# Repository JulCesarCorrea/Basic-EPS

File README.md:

# Missão Samaúma – Detecção Orbital de Pistas Clandestinas na Amazônia

## Introdução
A Amazônia desempenha um papel estratégico de extrema relevância global e nacional, abrigando a maior biodiversidade do planeta e recursos naturais de alto valor. Contudo, essa importância é 
ameaçada pela proliferação de pistas de pouso clandestinas, que funcionam como vetores para atividades ilícitas como garimpo ilegal, narcotráfico e desmatamento, comprometendo o equilíbrio ambiental,
social e a soberania nacional.
Estudos apontam que há mais pistas não homologadas do que oficiais na Amazônia Legal, formando uma infraestrutura paralela que impulsiona essas atividades ilegais.

Apesar dos esforços de fiscalização, o monitoramento por satélites convencionais enfrenta limitações significativas:
- Baixa frequência de revisita orbital, dificultando a detecção em tempo hábil.
- Alta latência entre a aquisição e o processamento das imagens.
- Custos elevados de obtenção e manutenção de imagens atualizadas.
- Diante desses desafios, a Missão Samaúma propõe o desenvolvimento de um CubeSat 1U de baixo custo com inteligência artificial embarcada capaz de realizar imageamento orbital autônomo e detecção
em tempo real de pistas clandestinas.

**O satélite processa as imagens diretamente em órbita e envia alertas com dados de localização e área estimada, reduzindo custos, latência e dependência de infraestrutura terrestre.
O projeto reforça a pesquisa em monitoramento ambiental com tecnologias acessíveis e contribui para o avanço da IA embarcada em CubeSats, com impacto direto na soberania e proteção da Amazônia.**

### Equipe e Responsabilidades

A Missão Samaúma é conduzida por dois estudantes de Engenharia de Computação do Instituto Nacional de Telecomunicações (INATEL), sob orientação técnica do Prof. Evandro César Vilas Boas.

### Membros, Funções e	Responsabilidades
- Mateus Ananias Duarte Lima	Software e IA embarcada	Desenvolvimento do algoritmo de detecção de pistas; implementação do sistema operacional de tempo real (RTOS); integração dos subsistemas via software.
- Daniele Letícia Pereira Sousa	Hardware e sistemas embarcados	Projeto e implementação dos subsistemas físicos (EPS, STR, Payload, COMMS, TCS, ADCS); integração e validação de hardware.

- Apesar da divisão de responsabilidades, o trabalho é conduzido de forma colaborativa e integrada, permitindo que ambos mantenham visão global do projeto e contribuam em múltiplas frentes técnicas.

## Descrição Operacional

A Missão Samaúma é estruturada em três etapas principais:
- Mapeamento e pesquisa inicial
- Identificação de áreas críticas com maior ocorrência de desmatamento, indicativas de potenciais pistas irregulares.
- Imageamento orbital via CubeSat
- Coleta de imagens nas regiões mapeadas, utilizando sensores ópticos embarcados.

### Processamento e análise por IA
O algoritmo embarcado processa as imagens diretamente no computador de bordo (OBC), distinguindo áreas de desmatamento comum de pistas clandestinas, e enviando alertas automáticos com coordenadas 
e área estimada.

## Tecnologias e Conceitos-Chave
- CubeSat 1U – Plataforma modular de baixo custo para missões orbitais.
- IA Embarcada (On-board Processing) – Reduz latência e dependência de links terrestres.
- RTOS (Real-Time Operating System) – Assegura eficiência e previsibilidade na execução das tarefas do satélite.
- Detecção Autônoma de Pistas – Uso de visão computacional e aprendizado de máquina para classificação de imagens orbitais.

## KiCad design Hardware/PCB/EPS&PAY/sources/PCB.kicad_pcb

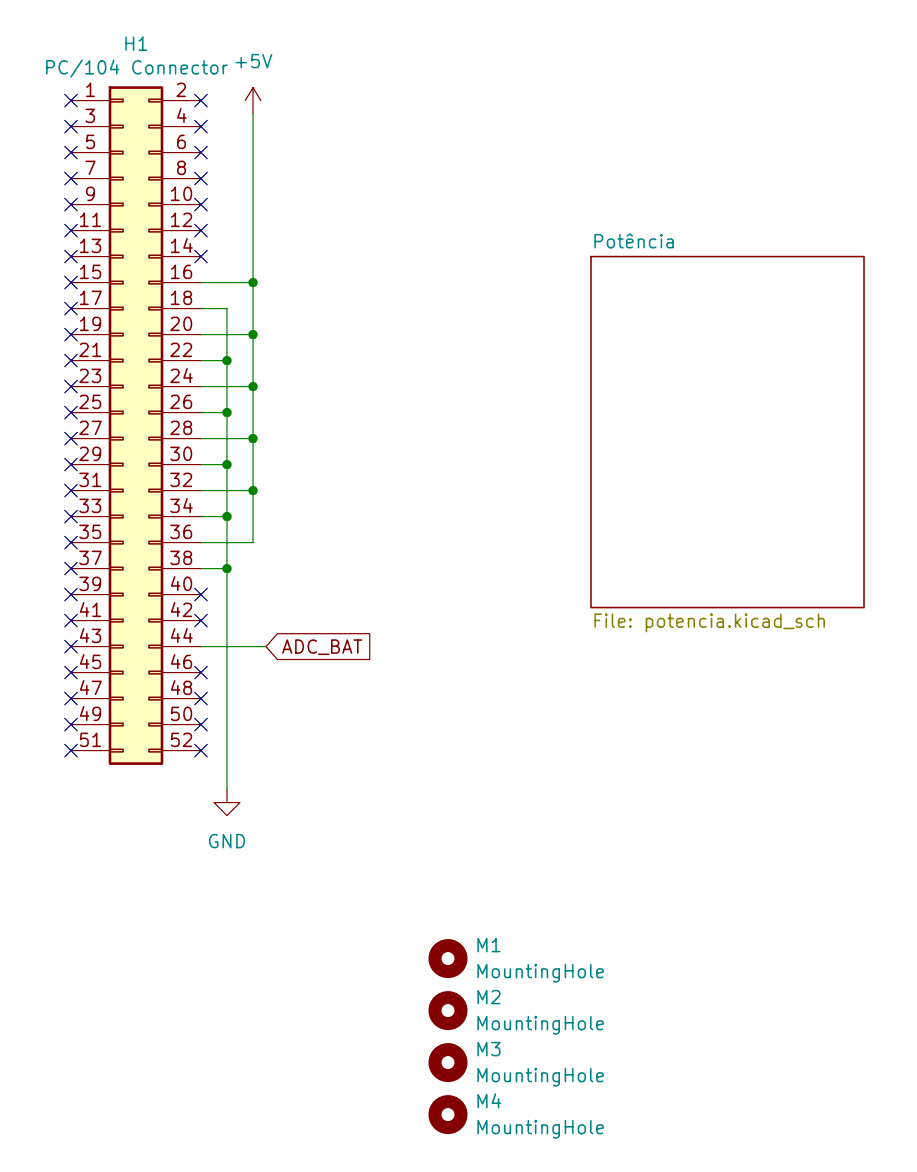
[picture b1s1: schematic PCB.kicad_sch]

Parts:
H1: PC/104 Connector; PinSocket_2x26_P2.54mm_Vertical
M1, M2, M3, M4: MountingHole; MountingHole_3.2mm_M3_Pad

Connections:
+5V: H1.16, H1.20, H1.24, H1.28, H1.32, H1.36; also elsewhere on the board
ADC_BAT: H1.44; also elsewhere on the board
GND: H1.18, H1.22, H1.26, H1.30, H1.34, H1.38; also elsewhere on the board

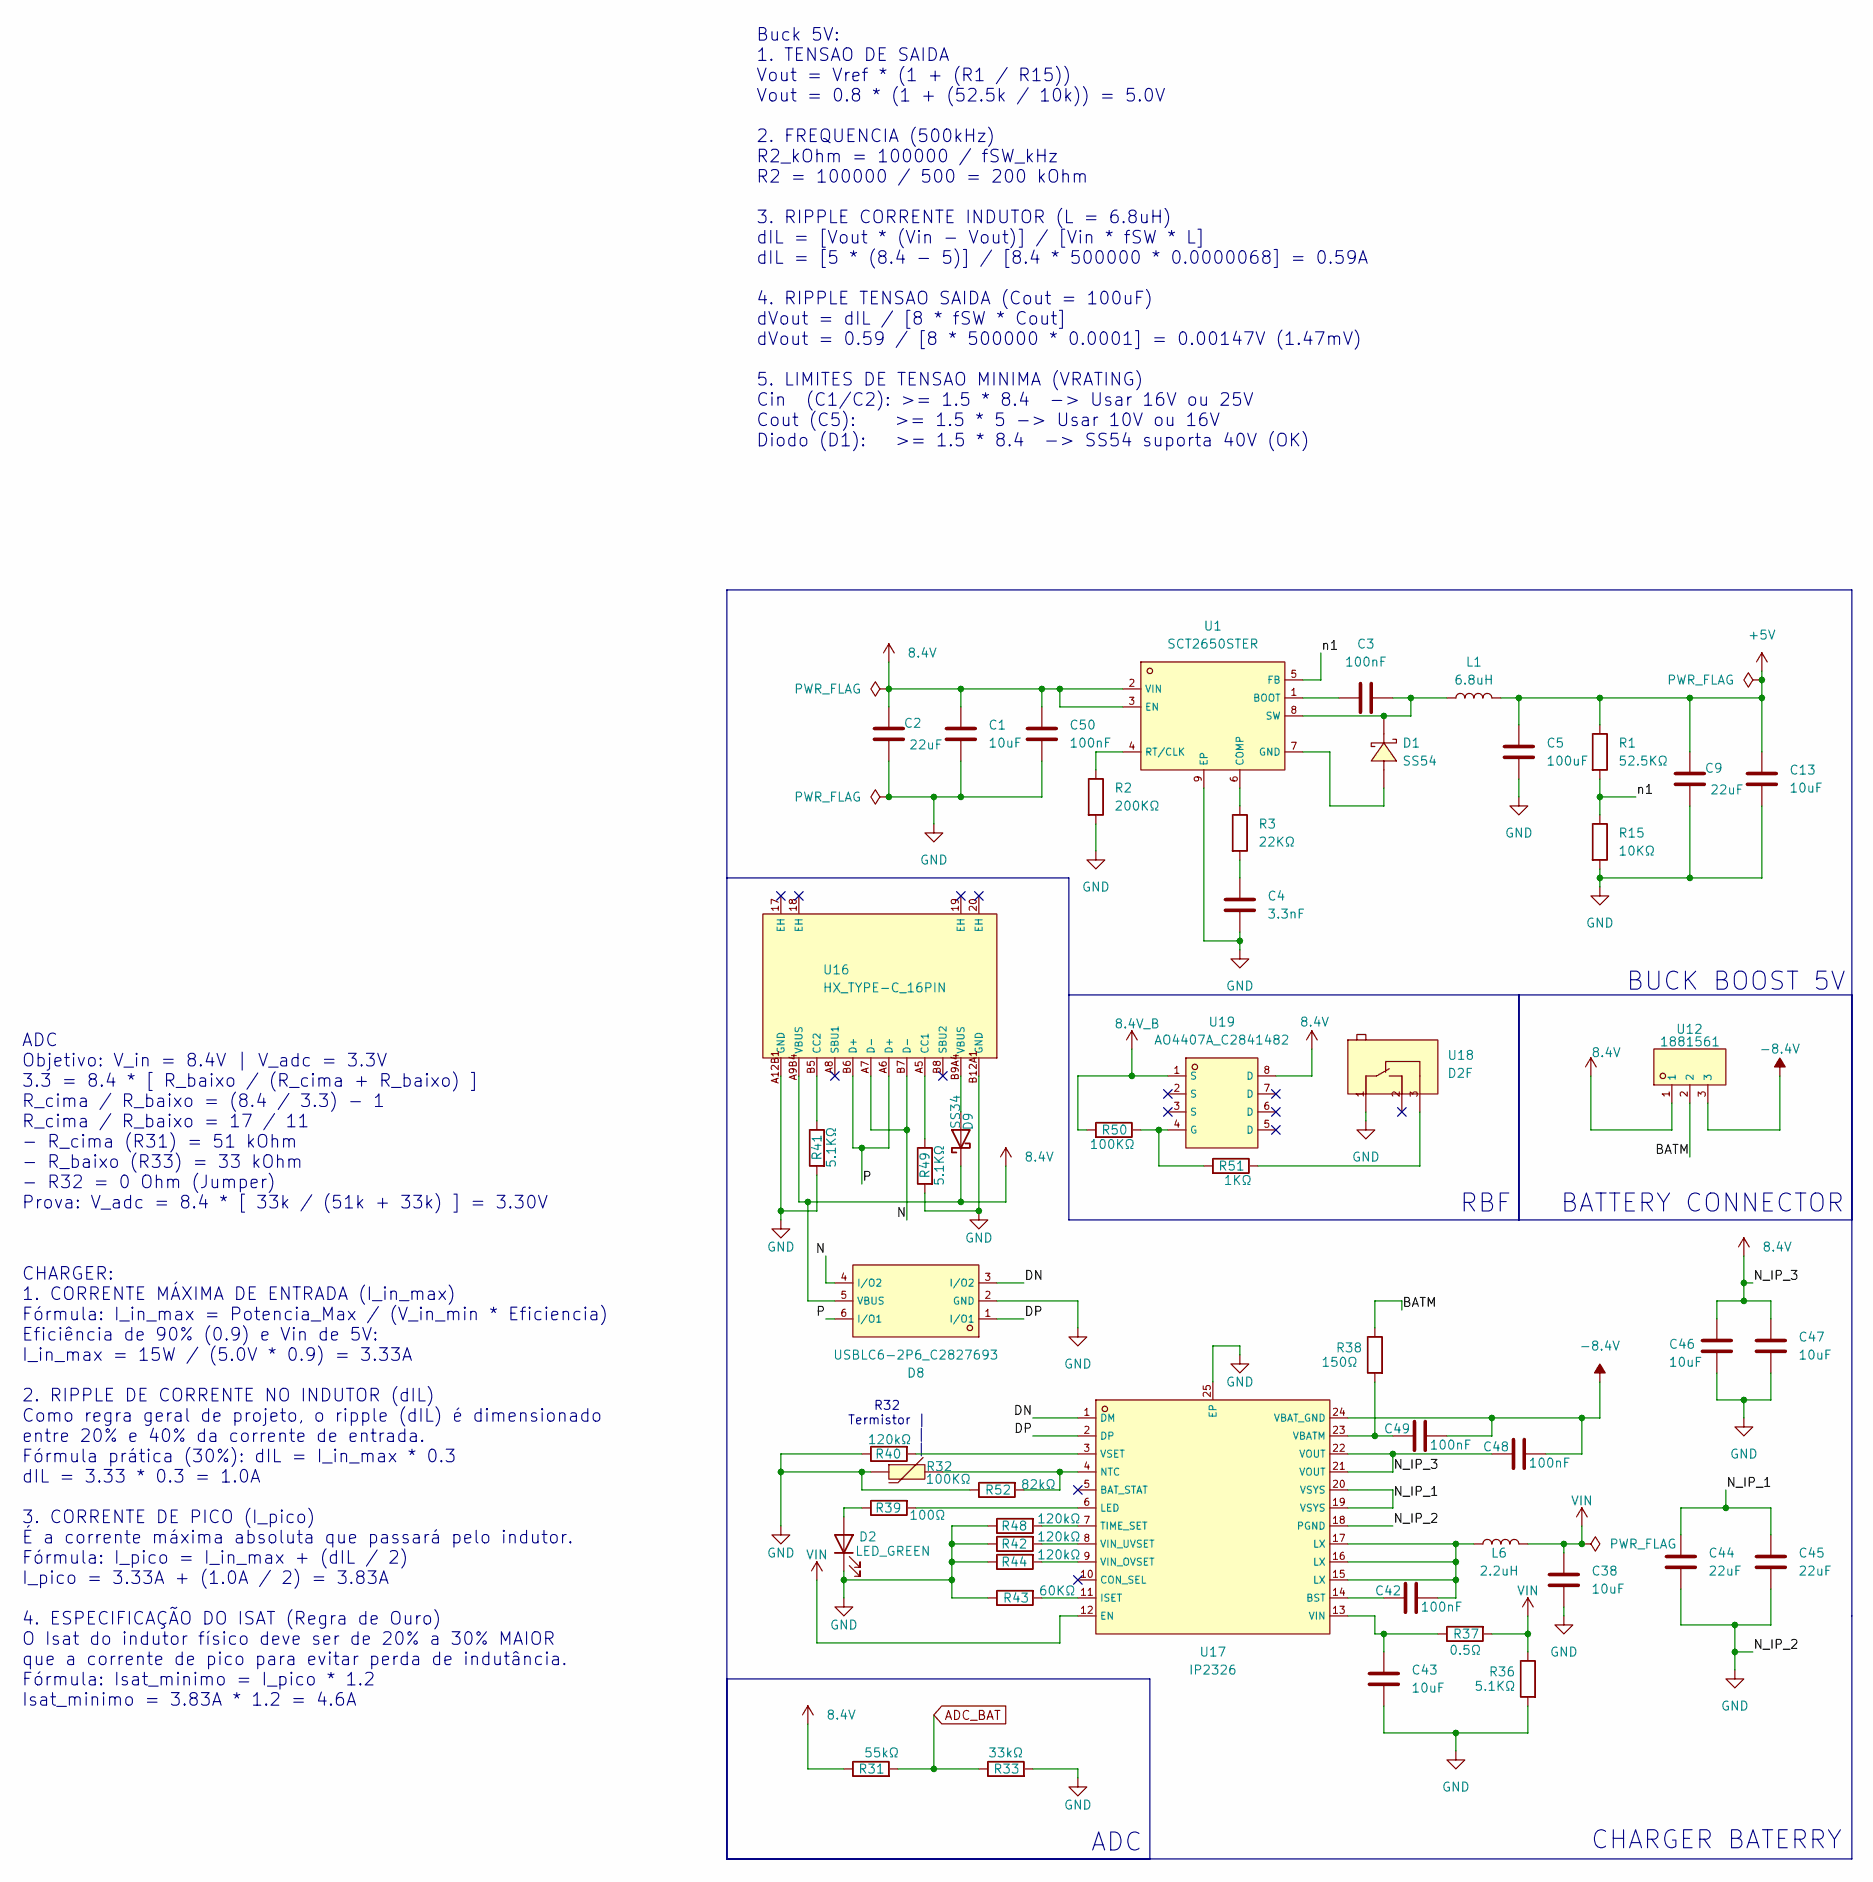
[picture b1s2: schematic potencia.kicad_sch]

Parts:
C1, C13, C38, C43, C46, C47: 10uF; C0805; LCSC C440198
C2, C9, C44, C45: 22uF; C1206; LCSC C3038553
C3, C42, C48, C49, C50: 100nF; C0603; LCSC C14663
C4: 3.3nF; C0603; LCSC C1613
C5: 100uF; C1206; LCSC C3038553
D1: SS54; SMB_L4.3-W3.6-LS5.4-RD; LCSC C5200096
D2: LED_GREEN; LED0603-FD; LCSC C19273151
D8: USBLC6-2P6_C2827693; SOT-666-6_L1.6-W1.2-P0.50-LS1.6-BL; LCSC C2827693
D9: SS34; D_SMA
L1: 6.8uH; IND-SMD_L5.4-W5.2; LCSC C718382
L6: 2.2uH; L1008; LCSC C42455362
R1: 52.5KΩ; R0402; LCSC C2998086
R2: 200KΩ; R0603; LCSC C2907009
R3: 22KΩ; R0603; LCSC C2907015
R15: 10KΩ; R0603; LCSC C98220
R31: 55kΩ; R_0603_1608Metric_Pad0.98x0.95mm_HandSolder; LCSC C2933461
R32: 100KΩ; R0603; LCSC C71280
R33: 33kΩ; R_1206_3216Metric_Pad1.30x1.75mm_HandSolder; LCSC C2933415
R36, R41, R49: 5.1KΩ; R0603; LCSC C2907044
R37: 0.5Ω; RES-SMD_L6.4-W3.2-R2512; LCSC C2904268
R38: 150Ω; R0603; LCSC C2933324
R39: 100Ω; R0603; LCSC C2906981
R40, R42, R44, R48: 120kΩ; R0603; LCSC C25808
R43: 60KΩ; R0603; LCSC C2907044
R50: 100KΩ; R0603; LCSC C14675
R51: 1KΩ; R0603; LCSC C22548
R52: 82kΩ; R0402; LCSC C2909388
U1: SCT2650STER; ESOP-8_L4.9-W3.9-P1.27-LS6.0-BL-EP-2; LCSC C2840771
U12: 1881561; CONN-TH_3P-P2.50_C3585554; LCSC C3585554
U16: HX_TYPE-C_16PIN; TYPE-C-SMD_HX-TYPE-C-16PIN; LCSC C5178539
U17: IP2326; VQFN-24_L4.0-W4.0-P0.50-BL-EP2.5; LCSC C2832094
U18: D2F; SW-TH_D2F-L; LCSC C397279
U19: AO4407A_C2841482; SOP-8_L5.0-W4.0-P1.27-LS6.0-BL; LCSC C2841482

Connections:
8.4V: C1.1, C2.1, C46.1, C47.1, C48.2, C50.2, D8.5 (VBUS), D9.1 (K), R31.1, U1.2 (VIN), U1.3 (EN), U12.1, U16.A9B4 (VBUS), U17.21 (VOUT), U17.22 (VOUT), U19.8 (D)
8.4V_B: R50.2, U19.1 (S)
+5V: C5.1, C9.1, C13.1, L1.2, R1.1; also elsewhere on the board
-8.4V: C48.1, C49.1, U12.3, U17.24 (VBAT_GND)
/Potência/BATM: R38.1, U12.2
/Potência/DN: D8.3 (I/O2), U17.1 (DM)
/Potência/DP: D8.1 (I/O1), U17.2 (DP)
/Potência/N: D8.4 (I/O2), U16.A7 (D-), U16.B7 (D-)
/Potência/N_IP_1: C44.1, C45.1, U17.19 (VSYS), U17.20 (VSYS)
/Potência/P: D8.6 (I/O1), U16.A6 (D+), U16.B6 (D+)
/Potência/n1: R1.2, R15.1, U1.5 (FB)
ADC_BAT: R31.2, R33.1; also elsewhere on the board
GND: C1.2, C2.2, C4.2, C5.2, C9.2, C13.2, C38.2, C43.2, C44.2, C45.2, C46.2, C47.2, C50.1, D2.1 (K), D8.2 (GND), R2.2, R15.2, R32.1, R33.2, R36.2, R40.1, R41.2, R42.1, R43.1, R44.1, R48.1, R49.2, R52.1, U1.9 (EP), U16.A12B1 (GND), U16.B12A1 (GND), U17.18 (PGND), U17.25 (EP), U18.1 (COM); also elsewhere on the board
unnamed: C4.1, R3.2
unnamed: C42.1, L6.1, U17.15 (LX), U17.16 (LX), U17.17 (LX)
unnamed: D2.2 (A), R39.1
unnamed: D9.2 (A), U16.B9A4 (VBUS)
unnamed: C3.1, U1.1 (BOOT)
unnamed: R3.1, U1.6 (COMP)
unnamed: D1.2, U1.7 (GND)
unnamed: R2.1, U1.4 (RT/CLK)
unnamed: C3.2, D1.1, L1.1, U1.8 (SW)
unnamed: R49.1, U16.A5 (CC1)
unnamed: R41.1, U16.B5 (CC2)
unnamed: C42.2, U17.14 (BST)
unnamed: R43.2, U17.11 (ISET)
unnamed: R39.2, U17.6 (LED)
unnamed: R32.2, R52.2, U17.4 (NTC)
unnamed: R48.2, U17.7 (TIME_SET)
unnamed: C49.2, R38.2, U17.23 (VBATM)
unnamed: C43.1, R37.1, U17.13 (VIN)
unnamed: R44.2, U17.9 (VIN_OVSET)
unnamed: R42.2, U17.8 (VIN_UVSET)
unnamed: R40.2, U17.3 (VSET)
unnamed: R51.1, U18.3 (NC)
unnamed: R50.1, R51.2, U19.4 (G)
VIN: C38.1, L6.2, R36.1, R37.2, U17.12 (EN)

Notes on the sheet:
CHARGER BATERRY
Buck 5V: 1. TENSAO DE SAIDA Vout = Vref * (1 + (R1 / R15)) Vout = 0.8 * (1 + (52.5k / 10k)) = 5.0V 2. FREQUENCIA (500kHz) R2_kOhm = 100000 / fSW_kHz R2 = 100000 / 500 = 200 kOhm 3. RIPPLE CORRENTE INDUTOR (L = 6.8uH) dIL = [Vout * (Vin - Vout)] / [Vin * fSW * L] dIL = [5 * (8.4 - 5)] / [8.4 * 50000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
BUCK BOOST 5V
ADC Objetivo: V_in = 8.4V | V_adc = 3.3V 3.3 = 8.4 * [ R_baixo / (R_cima + R_baixo) ] R_cima / R_baixo = (8.4 / 3.3) - 1 R_cima / R_baixo = 17 / 11 - R_cima (R31) = 51 kOhm - R_baixo (R33) = 33 kOhm - R32 = 0 Ohm (Jumper) Prova: V_adc = 8.4 * [ 33k / (51k + 33k) ] = 3.30V
CHARGER: 1. CORRENTE MÁXIMA DE ENTRADA (I_in_max) Fórmula: I_in_max = Potencia_Max / (V_in_min * Eficiencia) Eficiência de 90% (0.9) e Vin de 5V: I_in_max = 15W / (5.0V * 0.9) = 3.33A 2. RIPPLE DE CORRENTE NO INDUTOR (dIL) Como regra geral de projeto, o ripple (dIL) é dimensionado entre 20% e 40% d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
R32 Termistor | | |
BATTERY CONNECTOR
ADC
RBF

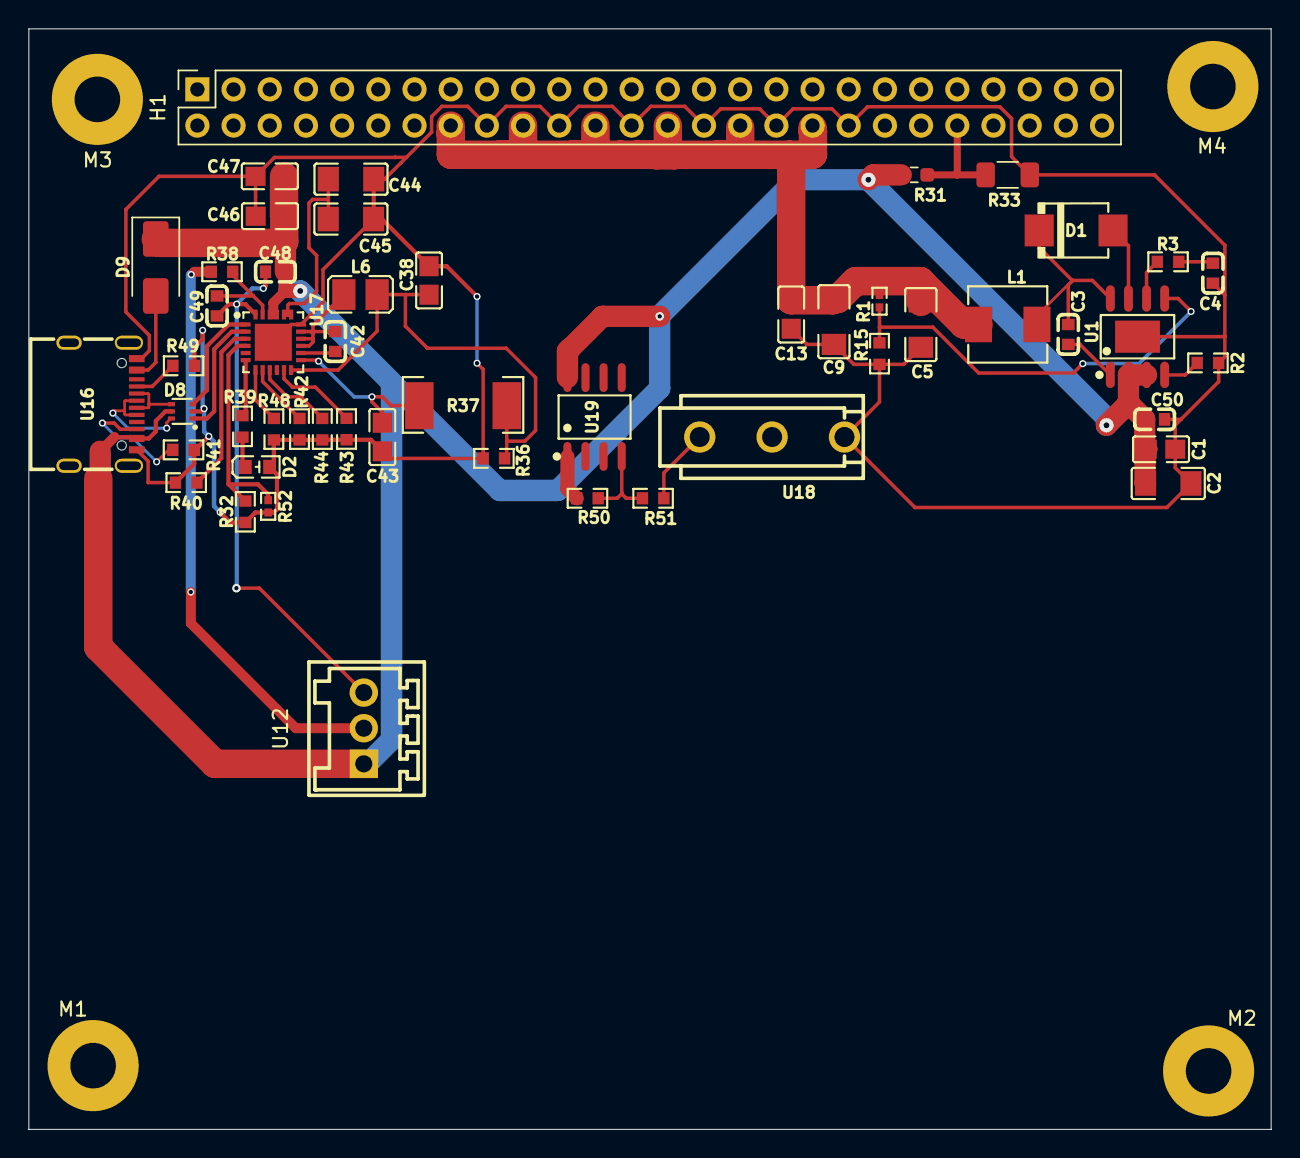
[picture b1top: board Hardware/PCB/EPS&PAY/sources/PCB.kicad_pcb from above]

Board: 2 copper layers, 87.2 x 77.2 mm, 55 parts (0 on the bottom side), 37 nets.

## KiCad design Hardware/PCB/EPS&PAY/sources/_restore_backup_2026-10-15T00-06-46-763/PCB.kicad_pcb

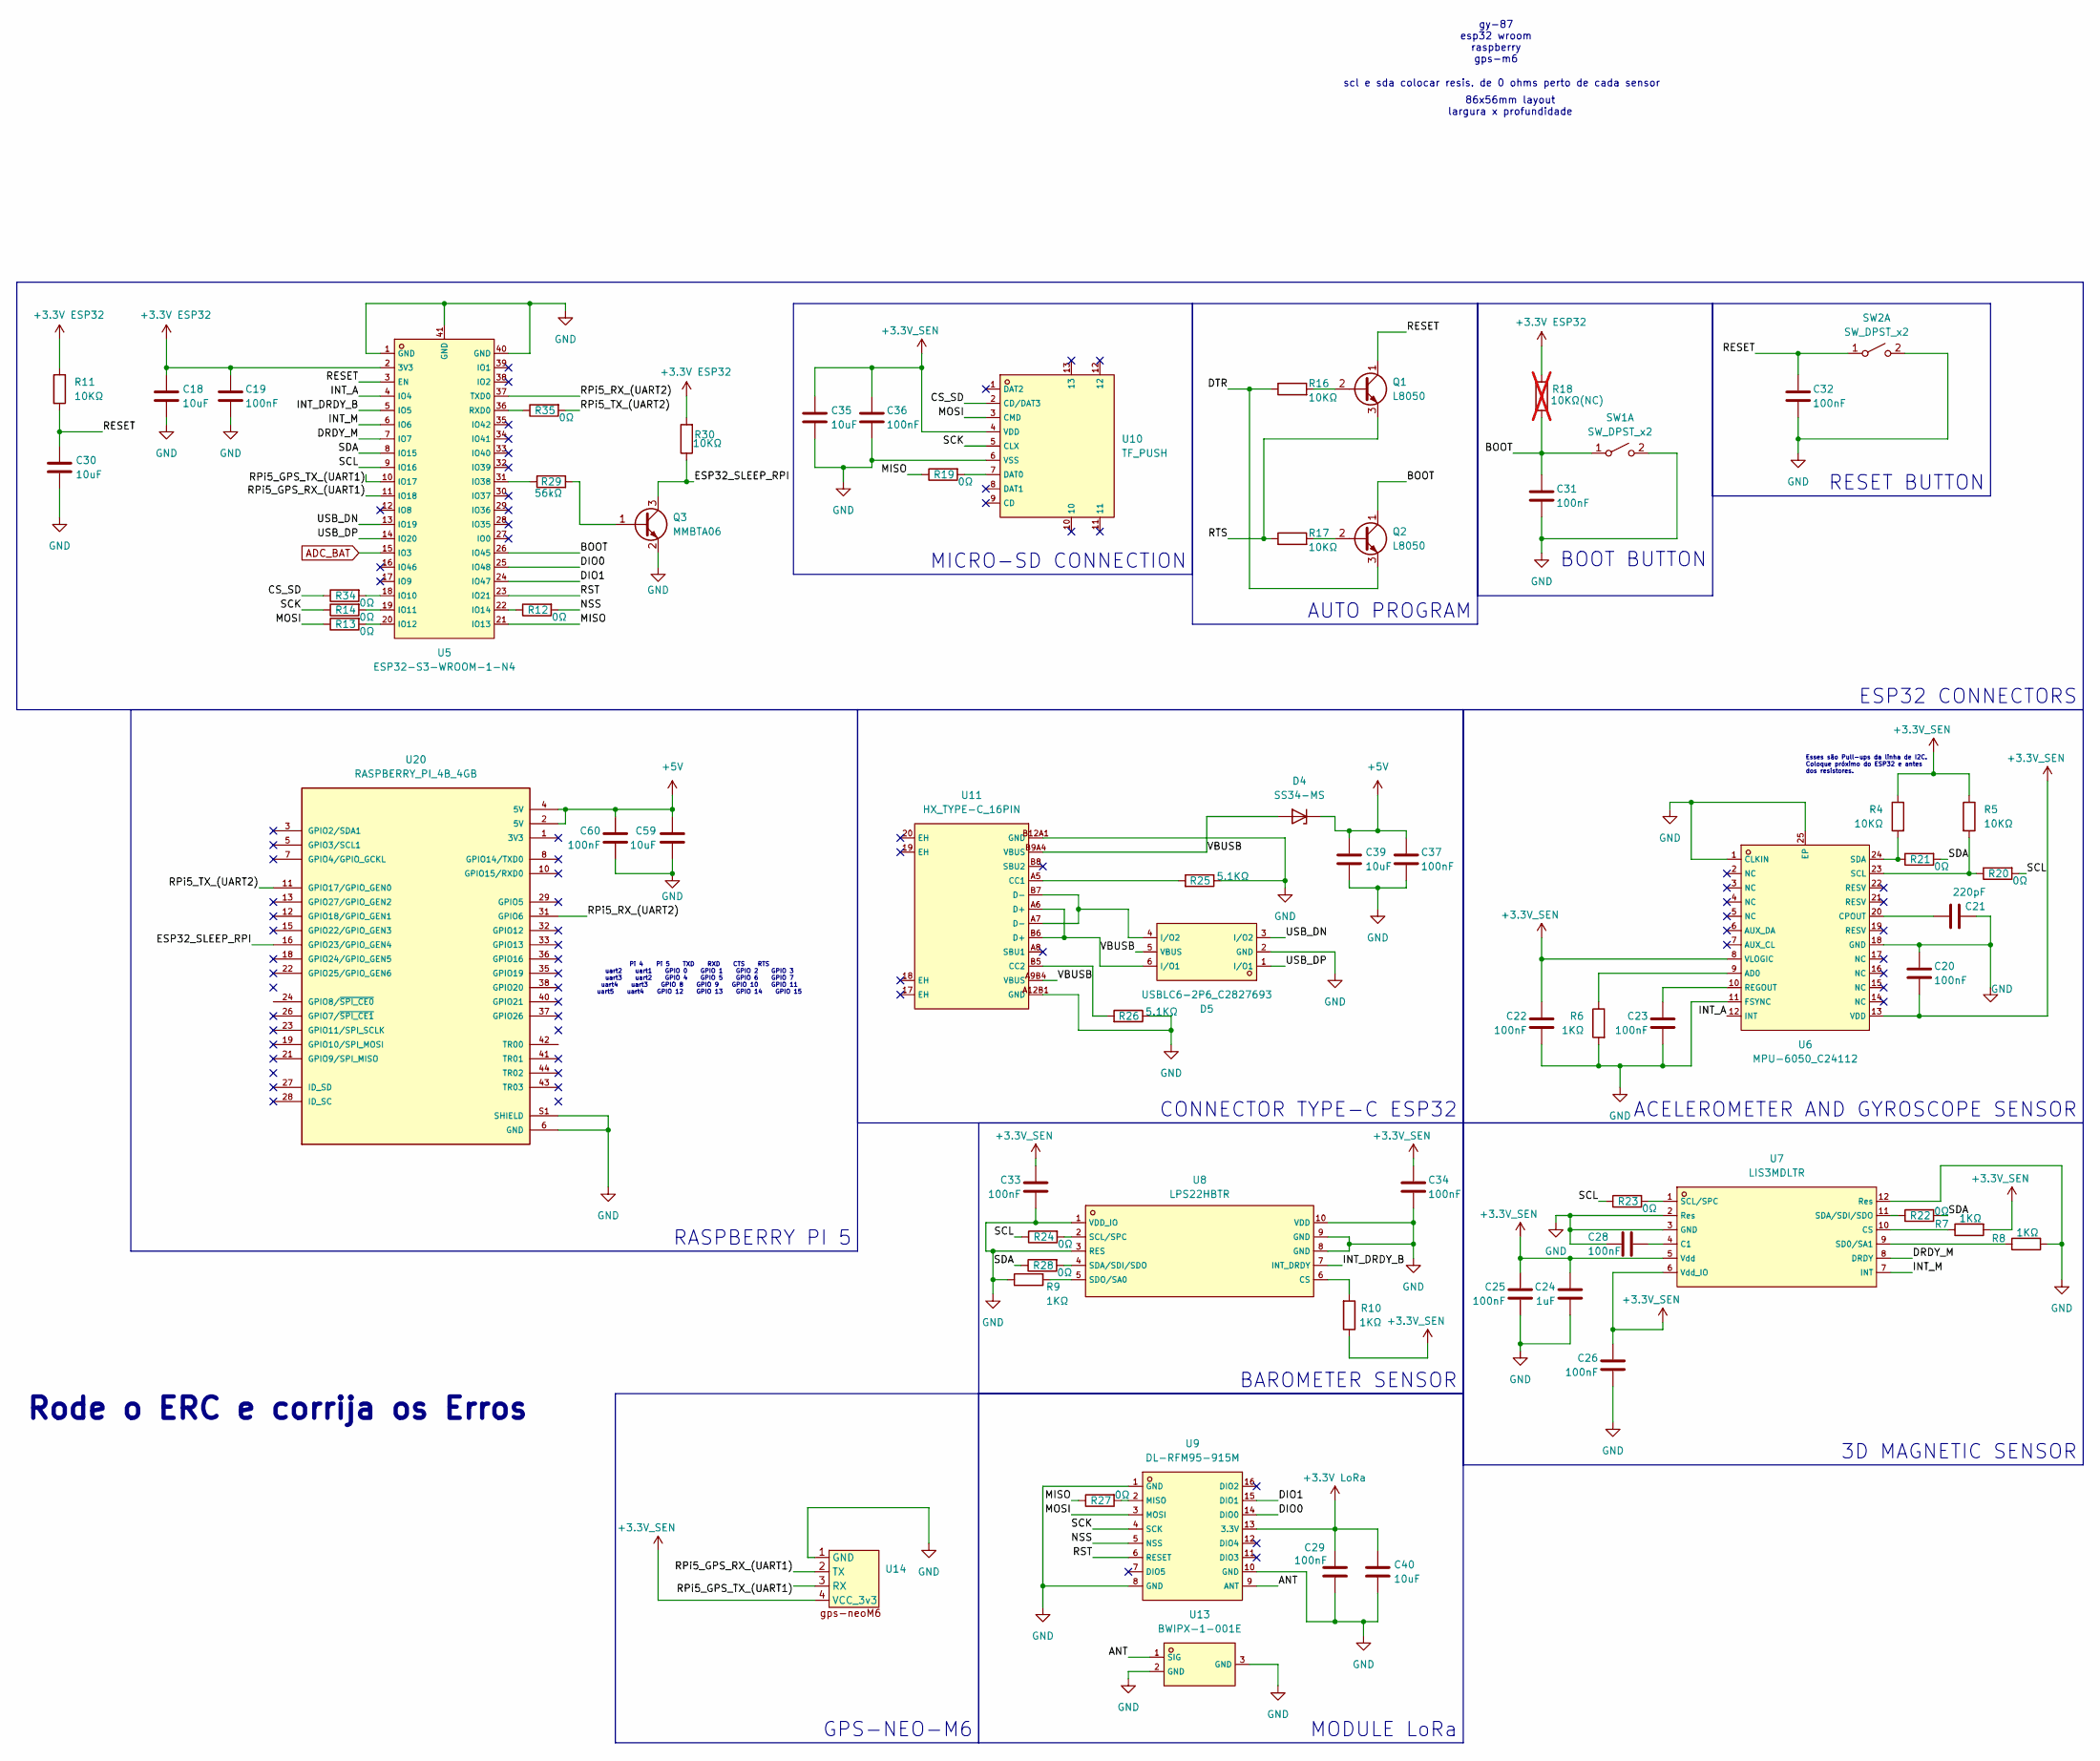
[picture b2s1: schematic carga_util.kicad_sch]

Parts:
C18, C30, C35, C39, C40, C59: 10uF; C0805; LCSC C440198
C19, C20, C22, C23, C25, C26, C28, C29, C31, C32, C33, C34, C36, C37, C60: 100nF; C0603; LCSC C14663
C21: 220pF; C0603; LCSC C1603
C24: 1uF; C0805; LCSC C541528
D4: SS34-MS; DO-214AC_L4.3-W2.7-LS5.0-RD; LCSC C2836396
D5: USBLC6-2P6_C2827693; SOT-666-6_L1.6-W1.2-P0.50-LS1.6-BL; LCSC C2827693
Q1, Q2: L8050; SOT-23-3_L2.9-W1.3-P1.90-LS2.4-BR; LCSC C49581
Q3: MMBTA06; SOT-23-3_L2.9-W1.6-P1.90-LS2.8-BR
R4, R5, R11, R16, R17, R30: 10KΩ; R0603; LCSC C98220
R6, R7, R8, R9, R10: 1KΩ; R0603; LCSC C22548
R12, R13, R14, R19, R20, R21, R22, R23, R24, R27, R28, R34, R35: 0Ω; R0603; LCSC C95177
R18: 10KΩ(NC); R0603; LCSC C98220; not fitted
R25, R26: 5.1KΩ; R0603; LCSC C2907044
R29: 56kΩ; R0603
SW1, SW2: SW_DPST_x2; SW-SMD_L3.9-W3.0-P4.45; LCSC C720477
U5: ESP32-S3-WROOM-1-N4; WIFIM-SMD_ESP32-S3-WROOM-1-N8; LCSC C2913197
U6: MPU-6050_C24112; QFN-24_L4.0-W4.0-P0.50-BL-EP2.7; LCSC C24112
U7: LIS3MDLTR; LGA-12_L2.0-W2.0-P0.50-BL; LCSC C478483
U8: LPS22HBTR; HLGA-10L_LPS22HBTR; LCSC C94049
U9: DL-RFM95-915M; LCC-16_L16.0-W16.0-P2.00-TL; LCSC C2844473
U10: TF_PUSH; TF-SMD_TF-PUSH; LCSC C393941
U11: HX_TYPE-C_16PIN; TYPE-C-SMD_HX-TYPE-C-16PIN; LCSC C5178539
U13: BWIPX-1-001E; IPEX-SMD_BWIPX-1-001E; LCSC C496552
U14: GPS_NEO-M6
U20: RASPBERRY_PI_4B_4GB; MODULE_RASPBERRY_PI_4B_4GB; PARTREV 4

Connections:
+3.3V ESP32: C18.1, C19.2, R11.1, R18.2, R30.2, U5.2 (3V3); also elsewhere on the board
+3.3V LoRa: C29.2, C40.1, U9.13 (3.3V); also elsewhere on the board
+3.3V_SEN: C20.1, C22.2, C24.2, C25.2, C26.2, C33.2, C34.2, C35.1, C36.2, R4.1, R5.1, R7.2, R10.1, U6.8 (VLOGIC), U6.13 (VDD), U7.5 (Vdd), U7.6 (Vdd_IO), U10.4 (VDD), U14.4 (VCC_3v3); also elsewhere on the board
+5V: C37.2, C39.1, C59.1, C60.2, D4.1 (K), U20.2 (5V), U20.4 (5V); also elsewhere on the board
/Carga Útil/ANT: U9.9 (ANT), U13.1 (SIG)
/Carga Útil/BOOT: C31.2, Q2.1 (C), R18.1, SW1.1 (A), U5.26 (IO45)
/Carga Útil/CS_SD: R34.1, U10.2 (CD/DAT3)
/Carga Útil/DIO0: U5.25 (IO48), U9.14 (DIO0)
/Carga Útil/DIO1: U5.24 (IO47), U9.15 (DIO1)
/Carga Útil/DRDY_M: U5.7 (IO7), U7.8 (DRDY)
/Carga Útil/DTR: Q2.3 (E), R16.1
/Carga Útil/ESP32_SLEEP_RPI: Q3.3 (C), R30.1, U20.16 (GPIO23/GPIO_GEN4)
/Carga Útil/INT_A: U5.4 (IO4), U6.12 (INT)
/Carga Útil/INT_DRDY_B: U5.5 (IO5), U8.7 (INT_DRDY)
/Carga Útil/INT_M: U5.6 (IO6), U7.7 (INT)
/Carga Útil/MISO: R19.1, R27.1, U5.21 (IO13)
/Carga Útil/MOSI: R13.1, U9.3 (MOSI), U10.3 (CMD)
/Carga Útil/NSS: R12.2, U9.5 (NSS)
/Carga Útil/RESET: C30.1, C32.2, Q1.1 (C), R11.2, SW2.1 (A), U5.3 (EN)
/Carga Útil/RPi5_GPS_RX_(UART1): U5.11 (IO18), U14.2 (TX)
/Carga Útil/RPi5_GPS_TX_(UART1): U5.10 (IO17), U14.3 (RX)
/Carga Útil/RPi5_RX_(UART2): U5.37 (TXD0), U20.31 (GPIO6)
/Carga Útil/RPi5_TX_(UART2): R35.2, U20.11 (GPIO17/GPIO_GEN0)
/Carga Útil/RST: U5.23 (IO21), U9.6 (RESET)
/Carga Útil/RTS: Q1.3 (E), R17.1
/Carga Útil/SCK: R14.1, U9.4 (SCK), U10.5 (CLX)
/Carga Útil/SCL: R20.2, R23.1, R24.1, U5.9 (IO16)
/Carga Útil/SDA: R21.2, R22.2, R28.1, U5.8 (IO15)
/Carga Útil/USB_DN: D5.3 (I/O2), U5.13 (IO19)
/Carga Útil/USB_DP: D5.1 (I/O1), U5.14 (IO20)
/Carga Útil/VBUSB: D4.2 (A), D5.5 (VBUS), U11.A9B4 (VBUS), U11.B9A4 (VBUS)
ADC_BAT: U5.15 (IO3); also elsewhere on the board
GND: C18.2, C19.1, C20.2, C21.1, C22.1, C23.1, C24.1, C25.1, C26.1, C28.1, C29.1, C30.2, C31.1, C32.1, C33.1, C34.1, C35.2, C36.1, C37.1, C39.2, C40.2, C59.2, C60.1, D5.2 (GND), Q3.2 (E), R6.2, R8.2, R9.1, R25.1, R26.1, SW1.2 (B), SW2.2 (B), U5.1 (GND), U5.40 (GND), U5.41 (GND), U6.1 (CLKIN), U6.11 (FSYNC), U6.18 (GND), U6.25 (EP), U7.2 (Res), U7.3 (GND), U7.12 (Res), U8.1 (VDD_IO), U8.3 (RES), U8.8 (GND), U8.9 (GND), U8.10 (VDD), U9.1 (GND), U9.8 (GND), U9.10 (GND), U10.6 (VSS), U11.A12B1 (GND), U11.B12A1 (GND), U13.2 (GND), U13.3 (GND), U14.1 (GND), U20.6 (GND), U20.9 (GND), U20.14 (GND), U20.20 (GND), U20.25 (GND), U20.30 (GND), U20.34 (GND), U20.39 (GND), U20.S1 (SHIELD), U20.S2 (SHIELD), U20.S3 (SHIELD), U20.S4 (SHIELD); also elsewhere on the board
unnamed: D5.6 (I/O1), U11.A6 (D+), U11.B6 (D+)
unnamed: D5.4 (I/O2), U11.A7 (D-), U11.B7 (D-)
unnamed: Q1.2 (B), R16.2
unnamed: Q2.2 (B), R17.2
unnamed: Q3.1 (B), R29.2
unnamed: R34.2, U5.18 (IO10)
unnamed: R14.2, U5.19 (IO11)
unnamed: R13.2, U5.20 (IO12)
unnamed: R12.1, U5.22 (IO14)
unnamed: R29.1, U5.31 (IO38)
unnamed: R35.1, U5.36 (RXD0)
unnamed: R6.1, U6.9 (AD0)
unnamed: C21.2, U6.20 (CPOUT)
unnamed: C23.2, U6.10 (REGOUT)
unnamed: R5.2, R20.1, U6.23 (SCL)
unnamed: R4.2, R21.1, U6.24 (SDA)
unnamed: C28.2, U7.4 (C1)
unnamed: R7.1, U7.10 (CS)
unnamed: R23.2, U7.1 (SCL/SPC)
unnamed: R8.1, U7.9 (SD0/SA1)
unnamed: R22.1, U7.11 (SDA/SDI/SDO)
unnamed: R10.2, U8.6 (CS)
unnamed: R24.2, U8.2 (SCL/SPC)
unnamed: R28.2, U8.4 (SDA/SDI/SDO)
unnamed: R9.2, U8.5 (SDO/SA0)
unnamed: R27.2, U9.2 (MISO)
unnamed: R19.2, U10.7 (DAT0)
unnamed: R25.2, U11.A5 (CC1)
unnamed: R26.2, U11.B5 (CC2)

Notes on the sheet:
scl e sda colocar resis. de 0 ohms perto de cada sensor
Pi 4 Pi 5 TXD RXD CTS RTS uart2 uart1 GPIO 0 GPIO 1 GPIO 2 GPIO 3 uart3 uart2 GPIO 4 GPIO 5 GPIO 6 GPIO 7 uart4 uart3 GPIO 8 GPIO 9 GPIO 10 GPIO 11 uart5 uart4 GPIO 12 GPIO 13 GPIO 14 GPIO 15
86x56mm layout largura x profundidade
Esses são Pull-ups da linha de I2C. Coloque próximo do ESP32 e antes dos resistores.
gy-87 esp32 wroom raspberry gps-m6
Rode o ERC e corrija os Erros
CONNECTOR TYPE-C ESP32
RASPBERRY PI 5
ACELEROMETER AND GYROSCOPE SENSOR
GPS-NEO-M6
BOOT BUTTON
MICRO-SD CONNECTION
AUTO PROGRAM
BAROMETER SENSOR
RESET BUTTON
ESP32 CONNECTORS
3D MAGNETIC SENSOR
MODULE LoRa
